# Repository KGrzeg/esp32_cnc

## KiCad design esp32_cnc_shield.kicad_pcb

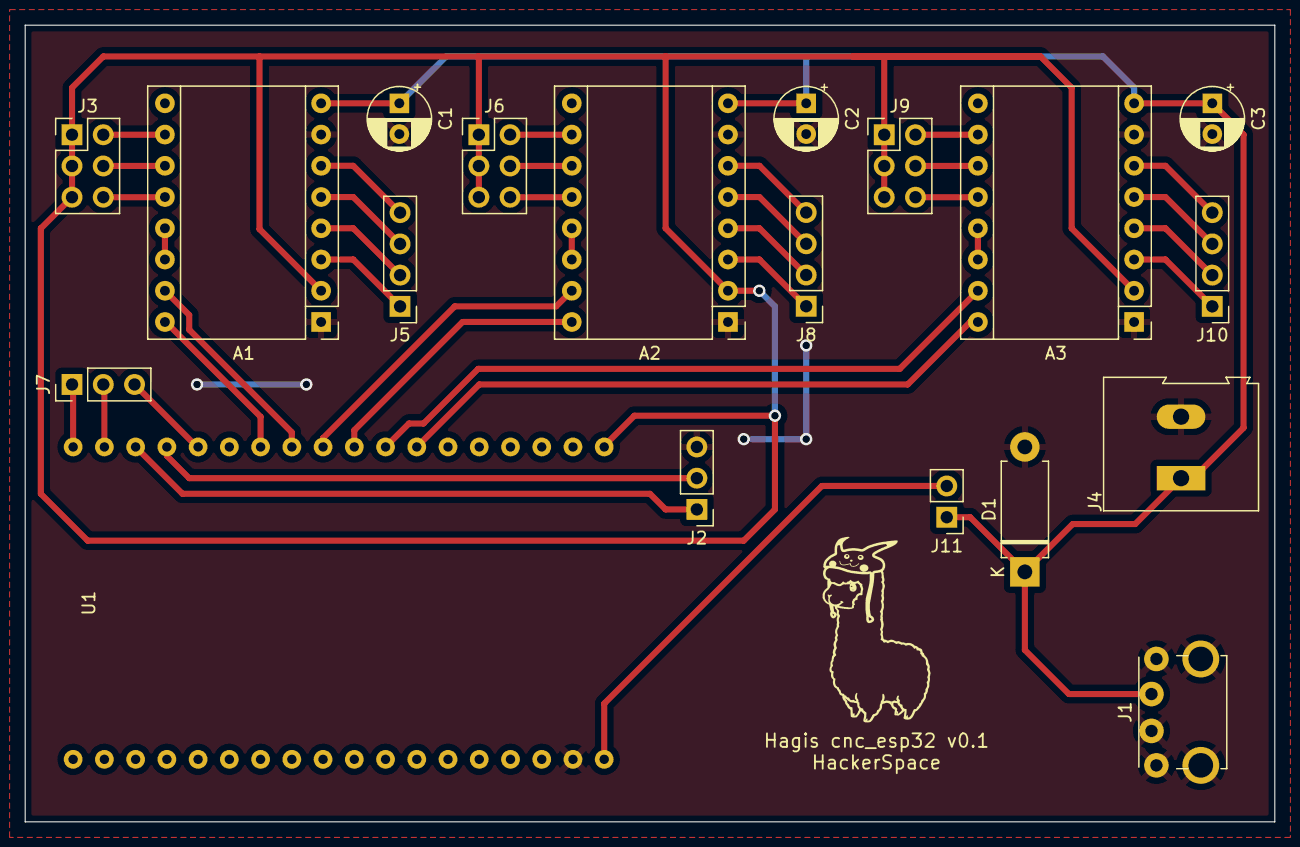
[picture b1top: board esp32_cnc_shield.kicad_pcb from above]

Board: 2 copper layers, 101.6 x 64.8 mm, 19 parts (0 on the bottom side), 39 nets.

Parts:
A1: X Axis; Pololu_Breakout-16_15.2x20.3mm
A2: Y Axis; Pololu_Breakout-16_15.2x20.3mm
A3: Z Axis; Pololu_Breakout-16_15.2x20.3mm
C1, C2, C3: 100u; CP_Radial_D5.0mm_P2.50mm
D1: D_Small_Filled; D_DO-15_P10.16mm_Horizontal
J1: USB C; USB_C_Cursed
J2: UART; PinHeader_1x03_P2.54mm_Vertical
J3: X Mode; PinHeader_2x03_P2.54mm_Vertical
J4: External Power; TerminalBlock_Altech_AK300-2_P5.00mm
J5: X Engine; PinHeader_1x04_P2.54mm_Vertical
J6: Y Mode; PinHeader_2x03_P2.54mm_Vertical
J7: Configuration; PinHeader_1x03_P2.54mm_Vertical
J8: Y Engine; PinHeader_1x04_P2.54mm_Vertical
J9: Z Mode; PinHeader_2x03_P2.54mm_Vertical
J10: Z Engine; PinHeader_1x04_P2.54mm_Vertical
J11: Future Shottky; PinHeader_1x02_P2.54mm_Vertical
U1: DOIT-ESP32-DEVKIT-V1; ESP32-DOIT-DEVKIT

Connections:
+3.3V: A1.2 (VDD), A2.2 (VDD), A3.2 (VDD), J3.1, J3.3, J3.5, J6.1, J6.3, J6.5, J9.1, J9.3, J9.5, U1.19 (3V3)
/rx: J2.2, U1.33 (GPIO3__UART0-RX)
/tx: J2.1, U1.34 (GPIO1_UART0-TX)
DIR_X: A1.16 (DIR), U1.30 (GPIO18_VSPI-CLK)
DIR_Y: A2.16 (DIR), U1.27 (GPIO16_UART2-RX)
DIR_Z: A3.16 (DIR), U1.25 (GPIO2_ADC2-CH2_RTC-GPIO12)
GND: A1.1 (GND), A1.7 (GND), A2.1 (GND), A2.7 (GND), A3.1 (GND), A3.7 (GND), C1.2, C2.2, C3.2, D1.2 (A), J1.2, J1.MP (MountPin), J2.3, J4.2, U1.17 (GND)
unnamed: A1.3 (1B), J5.1
unnamed: A1.4 (1A), J5.2
unnamed: A1.5 (2A), J5.3
unnamed: A1.6 (2B), J5.4
unnamed: A1.10 (MS1), J3.2
unnamed: A1.11 (MS2), J3.4
unnamed: A1.12 (MS3), J3.6
unnamed: A1.13 (~RESET), A1.14 (~SLEEP)
unnamed: A2.3 (1B), J8.1
unnamed: A2.4 (1A), J8.2
unnamed: A2.5 (2A), J8.3
unnamed: A2.6 (2B), J8.4
unnamed: A2.10 (MS1), J6.2
unnamed: A2.11 (MS2), J6.4
unnamed: A2.12 (MS3), J6.6
unnamed: A2.13 (~RESET), A2.14 (~SLEEP)
unnamed: A3.3 (1B), J10.1
unnamed: A3.4 (1A), J10.2
unnamed: A3.5 (2A), J10.3
unnamed: A3.6 (2B), J10.4
unnamed: A3.10 (MS1), J9.2
unnamed: A3.11 (MS2), J9.4
unnamed: A3.12 (MS3), J9.6
unnamed: A3.13 (~RESET), A3.14 (~SLEEP)
STEP_X: A1.15 (STEP), U1.29 (GPIO5_VSPI-CS0)
STEP_Y: A2.15 (STEP), U1.28 (GPIO17_UART2-TX)
STEP_Z: A3.15 (STEP), U1.26 (GPIO4_ADC2-CH0_RTC-GPIO10)
STOP_X: J7.1, U1.36 (GPIO23_VSPI-MOSI)
STOP_Y: J7.2, U1.35 (GPIO22_I2C-SCL)
STOP_Z: J7.3, U1.32 (GPIO21_I2C-SDA)
VCC: A1.8 (VMOT), A2.8 (VMOT), A3.8 (VMOT), C1.1, C2.1, C3.1, D1.1 (K), J1.1, J4.1, J11.1
VIN: J11.2, U1.18 (VIN)

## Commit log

2022-08-18 Schematic 1st version
2022-08-20 Cringe USB
2022-08-20 Make it pretty
2022-08-20 Add pseudo shottky

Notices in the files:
esp32_cnc_shield.kicad_pcb:
License: CC BY 4.0
